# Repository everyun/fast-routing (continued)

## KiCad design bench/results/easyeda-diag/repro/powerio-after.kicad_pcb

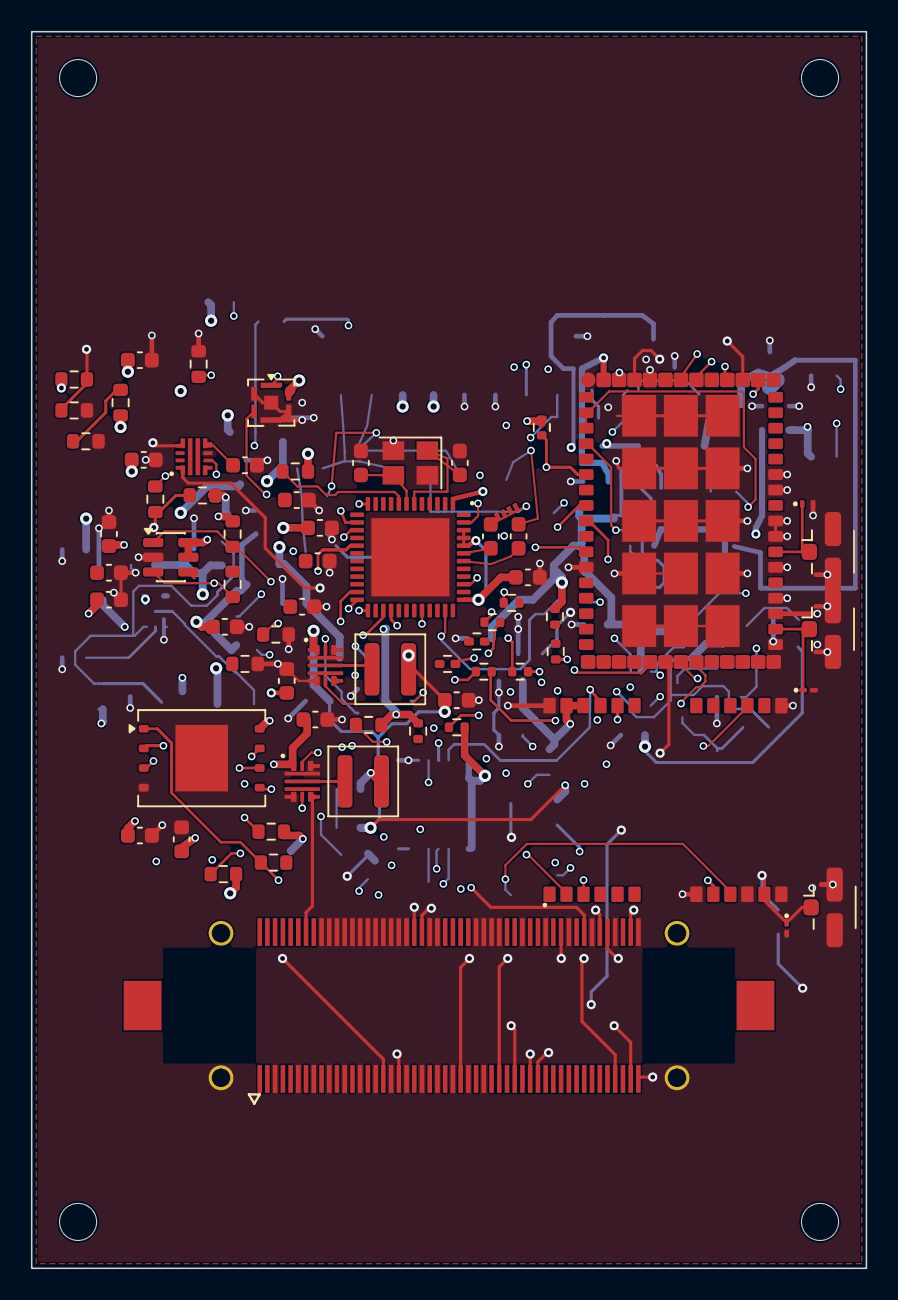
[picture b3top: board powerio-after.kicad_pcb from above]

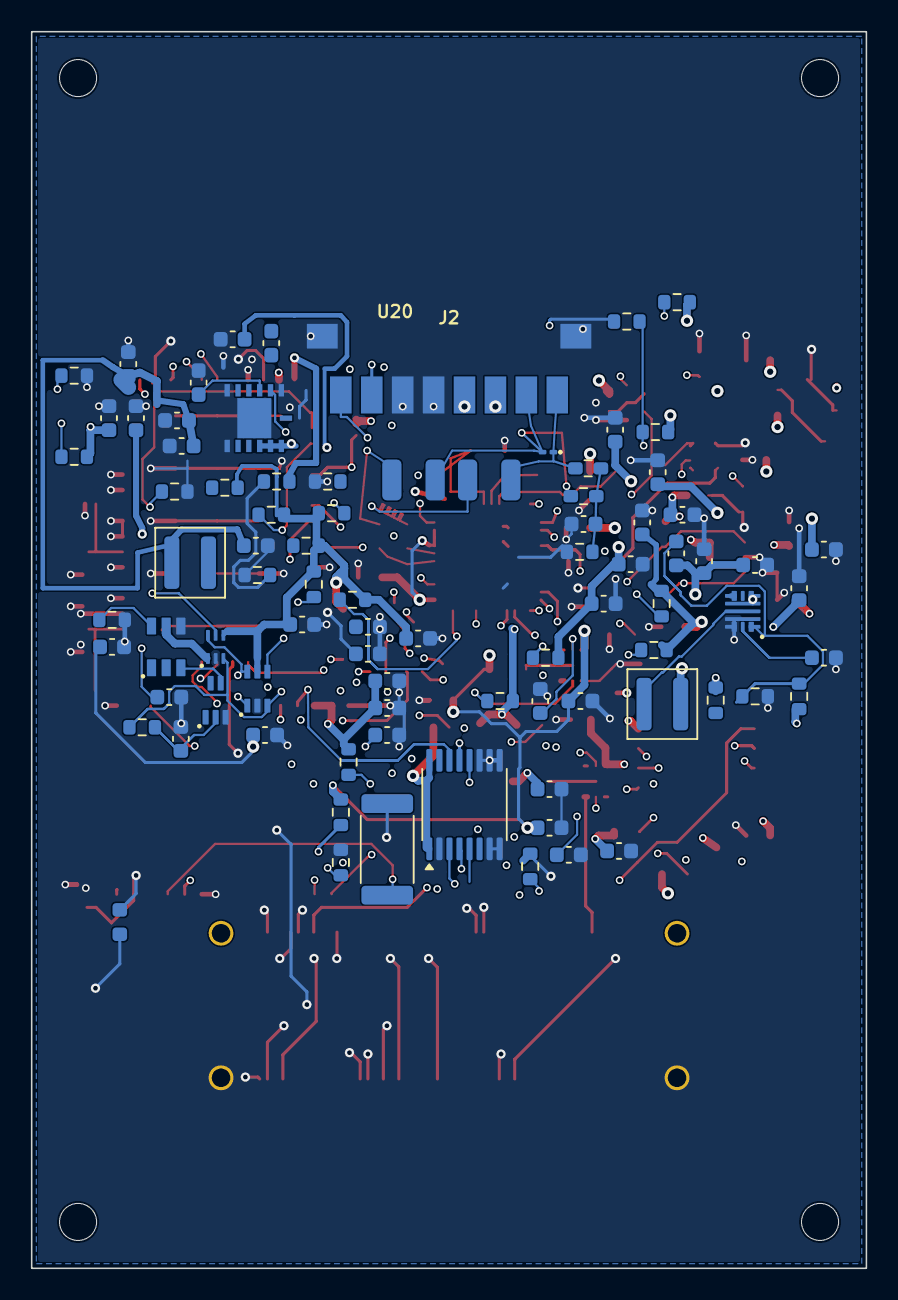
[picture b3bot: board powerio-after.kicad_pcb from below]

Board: 6 copper layers, 54.0 x 80.0 mm, 156 parts (85 on the bottom side), 117 nets.

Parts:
C101: 4.7nF; PIO_C101
C102: 22uF; PIO_C102
C103: 22uF; PIO_C103
C201: 22uF; PIO_C201
C202: 22uF; PIO_C202
C203: 22uF; PIO_C203
C204: 10uF; PIO_C204
C205: 4.7nF; PIO_C205
C301: 22uF; PIO_C301
C302: 22uF; PIO_C302
C303: 10uF; PIO_C303
C304: 4.7nF; PIO_C304
C409: 10uF; PIO_C409
C410: 100nF; PIO_C410
C411: 100nF; PIO_C411
C412: 100nF; PIO_C412
C422: 18pF; PIO_C422
C423: 18pF; PIO_C423
C430: 100nF; PIO_C430
C431: 100nF; PIO_C431
C432: 4.7nF; PIO_C432
C441: 100nF; PIO_C441
C442: 100nF; PIO_C442
C443: 100nF; PIO_C443
C444: 100nF; PIO_C444
C501: 100nF; PIO_C501
C502: 1uF; PIO_C502
C601: 10uF; PIO_C601
C602: 100nF; PIO_C602
C603: 100nF; PIO_C603
C604: 1uF; PIO_C604
C605: 1uF; PIO_C605
C606: 100nF; PIO_C606
C607: 100nF; PIO_C607
C608: 100nF; PIO_C608
C609: 4.7nF; PIO_C609
C610: 4.7nF; PIO_C610
C611: 47nF; PIO_C611
C612: 100nF; PIO_C612
C701: 1uF; PIO_C701
C702: 100nF; PIO_C702
C703: 100nF; PIO_C703
C901: 100nF; PIO_C901
C902: 4.7uF; PIO_C902
C1101: 100nF; PIO_C1101
C1102: 1nF; PIO_C1102
C1103: 4.7nF; PIO_C1103
C1301: 100nF; PIO_C1301
C1302: 100nF; PIO_C1302
C1501: 22uF; PIO_C1501
C1502: 22uF; PIO_C1502
C1503: 22uF; PIO_C1503
C1504: 10uF; PIO_C1504
C1505: 10pF; PIO_C1505
C1506: 4.7nF; PIO_C1506
C2001: 22uF; PIO_C2001
C2002: 22uF; PIO_C2002
C2003: 22uF; PIO_C2003
C2004: 100nF; PIO_C2004
C2005: 1uF; PIO_C2005
D430: PESD2ETH100-T; PIO_D430
D601: ESD; PIO_D601
D602: ESD; PIO_D602
D701: ESD; PIO_D701
J1: FX23L-100S-0.5SV-SEL; PIO_J1
J2: PIO-HYBRID-8P-RA-PIGTAIL; PIO_J2
J3: U.FL-R-SMT-1(10); PIO_J3
J4: U.FL-R-SMT-1(10); PIO_J4
J5: U.FL-R-SMT-1(10); PIO_J5
L201: 0.47uH; PIO_L201
L301: 0.47uH; PIO_L301
L430: 80uH; PIO_L430
L431: 80uH; PIO_L431
L701: 27nH; PIO_L701
L1501: 0.47uH; PIO_L1501
L2001: 4.7uH; PIO_L2001
MH1: M2_NPTH_D2.4; PIO_MH1
MH2: M2_NPTH_D2.4; PIO_MH2
MH3: M2_NPTH_D2.4; PIO_MH3
MH4: M2_NPTH_D2.4; PIO_MH4
R101: 604k; PIO_R101
R102: 100k; PIO_R102
R103: 1.27M; PIO_R103
R104: 100k; PIO_R104
R105: 1.00k; PIO_R105
R106: 10k; PIO_R106
R107: 0R; PIO_R107
R201: 10k; PIO_R201
R301: 10k; PIO_R301
R401: 1k; PIO_R401
R402: 4.7k; PIO_R402
R403: 10k; PIO_R403
R411: 33R; PIO_R411
R412: 33R; PIO_R412
R413: 33R; PIO_R413
R414: 33R; PIO_R414
R415: 33R; PIO_R415
R416: 33R; PIO_R416
R430: 12.1k; PIO_R430
R431: 10k; PIO_R431
R432: 10k; PIO_R432
R433: 10k; PIO_R433
R434: 1.00k; PIO_R434
R435: 1.00k; PIO_R435
R436: 100k; PIO_R436
R501: 4.7k; PIO_R501
R502: 4.7k; PIO_R502
R503: 4.7k; PIO_R503
R601: 100k; PIO_R601
R602: 100k; PIO_R602
R603: 100k; PIO_R603
R604: 100k; PIO_R604
R605: 100k; PIO_R605
R606: 47k; PIO_R606
R607: 47k; PIO_R607
R608: 47k; PIO_R608
R609: 47k; PIO_R609
R610: 47k; PIO_R610
R611: 10k; PIO_R611
R612: 10k; PIO_R612
R615: 100k; PIO_R615
R701: 100k; PIO_R701
R702: 10k; PIO_R702
R703: 100k; PIO_R703
R704: 22R; PIO_R704
R901: 2k; PIO_R901
R902: 2k; PIO_R902
R1101: 10k; PIO_R1101
R1102: 10k; PIO_R1102
R1501: 47.5k; PIO_R1501
R1502: 15k; PIO_R1502
R1503: 10k; PIO_R1503
R1601: 0R; PIO_R1601
R1602: 10k; PIO_R1602
R1603: 10k; PIO_R1603
R2001: 100k; PIO_R2001
R2002: 24.9k; PIO_R2002
R2003: 200k; PIO_R2003
R2004: 10k; PIO_R2004
U1: TPS259470ARPWR; PIO_U1
U2: TPS628133HQWRWYRQ1; PIO_U2
U3: TPS628112MQWRWYRQ1; PIO_U3
U4: LAN8871-V/PUAVAO; PIO_U4
U5: MX25U51245GZ4J00; PIO_U5
U6: JODY-W263-01A; PIO_U6
U7: NEO-M9L-01A-01; PIO_U7
U9: ILPS28QSWTR; PIO_U9
U11: TPS3808G18DBVR; PIO_U11
U13: SN74AXC4T774QPWRQ1; PIO_U13
U15: TPS62812QWRWYRQ1; PIO_U15
U16: TPS22995HQDDCRQ1; PIO_U16
U17: SN74LVC1G11IDCKRQ1; PIO_U17
U18: TPS389018QDSERQ1; PIO_U18
U19: SN74LVC1G17QDCKRQ1; PIO_U19
U20: LM61460AFSQRJRRQ1; PIO_U20
Y401: 25MHz CL12pF; PIO_Y401

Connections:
+1V8_AUX: C302.1, C303.1, C409.1, C410.1, C411.1, C412.1, C501.1, C502.1, C603.1, C605.1, C607.1, C608.1, C612.1, C1101.1, C1103.1, C1301.1, L301.2, R106.2, R201.2, R301.2, R401.2, R402.2, R403.2, R431.2, R433.2, R501.2, R502.2, R503.2, R602.2, R603.2, R604.2, R606.2, R607.2, R608.2, R609.2, R610.2, R612.2, R1101.2, R1102.2, R1503.2, R1602.2, R1603.2, R2004.2, U3.5, U4.13, U4.20, U4.36, U5.8, U6.3, U11.5, U11.6, U13.1, U13.16, U16.2, U17.5, U18.4, U19.5
+1V8_JODY_SW: C604.1, C610.1, U6.4, U16.5, U18.1
+2V5_PHY: C441.1, C442.1, C443.1, C444.1, C1502.1, C1503.1, C1504.1, C1505.1, L1501.2, R1501.1, U4.1, U4.5, U4.9, U4.10, U4.19, U4.29, U4.37, U4.41, U4.44, U4.45, U4.46, U4.48
+3V3_AUX: C202.1, C203.1, C204.1, C701.1, C702.1, C901.1, C902.1, C1302.1, L201.2, R701.2, R702.2, R901.2, R902.2, U2.5, U7.22, U7.23, U9.6, U13.15
+5V_PROTECTED: C103.1, C201.1, C301.1, C601.1, C602.1, C606.1, C1501.1, C2002.1, C2003.1, J1.1, J1.2, J1.3, J1.4, J1.5, J1.6, J1.7, J1.8, J1.P1, J1.P2, L2001.2, R2001.1, U2.2, U2.8, U3.2, U3.8, U6.2, U15.1, U15.2, U15.8, U16.1
+12V_PROTECTED: C2001.1, U1.6, U20.1, U20.2, U20.3
+12V_TAIL_PROTECTED: C102.1, J2.3, J2.4, R101.1, R103.1, U1.5
ACC_ON: J1.90, R1601.2, R1602.1
ACC_STATUS: J2.7, R1601.1
BT_DEV_WAKE_FROM_SOC: J1.21, U6.11
BT_HOST_WAKE_TO_SOC: J1.22, U6.12
BT_REG_ON_FROM_SOC: J1.85, U6.33
BT_RF: D602.1, J4.1, U6.24
BT_UART_CTS_N_FROM_SOC: J1.83, U6.39
BT_UART_RTS_N_TO_SOC: J1.84, U6.38
BT_UART_RX_TO_SOC: J1.82, U6.36
BT_UART_TX_FROM_SOC: J1.81, U6.37
EFUSE_DVDT: C101.1, U1.7
EFUSE_EN_UVLO: R101.2, R102.1, U1.1
EFUSE_ILM: R105.1, U1.9
EFUSE_OVLO: R103.2, R104.1, U1.2
EPHY0_RSTN: J1.54, R403.1, U4.39
FB_2V5_PHY: C1505.2, R1501.2, R1502.1, U15.5
GND: C101.2, C102.2, C103.2, C201.2, C202.2, C203.2, C204.2, C205.2, C301.2, C302.2, C303.2, C304.2, C409.2, C410.2, C411.2, C412.2, C422.2, C423.2, C432.2, C441.2, C442.2, C443.2, C444.2, C501.2, C502.2, C601.2, C602.2, C603.2, C604.2, C605.2, C606.2, C607.2, C608.2, C609.2, C610.2, C611.2, C612.2, C701.2, C702.2, C703.2, C901.2, C902.2, C1101.2, C1102.2, C1103.2, C1301.2, C1302.2, C1501.2, C1502.2, C1503.2, C1504.2, C1506.2, C2001.2, C2002.2, C2003.2, C2005.2, D601.2, D602.2, D701.2, J1.9, J1.10, J1.11, J1.12, J1.13, J1.14, J1.15, J1.16, J1.17, J1.18, J1.19, J1.20, J1.23, J1.24, J1.29, J1.30, J1.31, J1.32, J1.35, J1.38, J1.41, J1.44, J1.47, J1.50, J1.53, J1.56, J1.58, J1.60, J1.62, J1.64, J1.66, J1.68, J1.70, J1.72, J1.74, J1.76, J1.78, J1.80, J1.P3, J1.P4, J2.5, J2.6, J2.SH1, J2.SH2, J3.2, J4.2, J5.2, R102.2, R104.2, R105.2, R430.2, R432.2, R436.2, R601.2, R605.2, R611.2, R703.2, R1502.2, R2002.2, R2003.2, U1.8, U2.1, U2.4, U2.7, U3.1, U3.4, U3.7, U4.49, U5.4, U5.9, U6.1, U6.5, U6.19, U6.20, U6.22, U6.23, U6.25, U6.27, U6.28, U6.30, U6.31, U6.49, U6.61, U6.62, U6.63, U6.64, U6.65, U6.66, U6.67, U6.68, U6.69, U6.70, U6.71, U6.72, U6.73, U6.74, U6.75, U7.7, U7.10, U7.12, U7.13, U7.24, U9.2, U9.4, U9.5, U9.7, U11.2, U13.2, U13.7, U13.8, U13.9, U13.10, U13.11, U15.4, U15.7, U16.4, U17.2, U18.2, U19.3, U20.6, U20.7, U20.12, U20.14, Y401.2, Y401.4
GNSS_1PPS_TO_SOC: J1.97, U13.5
GNSS_BIAS_LIMITED: L701.1, R704.2
GNSS_DIR: R703.1, U7.15
GNSS_DSEL_HI: R701.1, U7.2
GNSS_RESET_N: R702.1, U7.8
GNSS_RF: D701.1, J5.1, L701.2, U7.11
GNSS_RX_3V3: U7.21, U13.14
GNSS_TIMEPULSE_3V3: U7.3, U13.12
GNSS_TX_3V3: U7.20, U13.13
GNSS_TX_TO_SOC_UART2_RX: J1.95, U13.4
GNSS_VCC_RF: C703.1, R704.1, U7.9
I2C11_SCL_3V3_OD: J1.93, R902.1, U9.3
I2C11_SDA_3V3_OD: J1.94, R901.1, U9.1
JODY_1V8_CT: C609.1, U18.5
JODY_1V8_GOOD: R612.1, U17.6, U18.6
JODY_1V8_RT: R611.1, U16.6
JODY_CONFIG0_PD: R601.1, U6.7
JODY_CONFIG1_HI: R602.1, U6.8
JODY_CONFIG2_DNI: R603.1, U6.6
JODY_PDN_GATED: R605.1, U6.58, U6.59, U17.4
JODY_PG_DELAYED: U16.3, U19.4
JODY_PG_DELAY_RC: C611.1, R615.2, U19.2
JODY_PG_N: R604.1, R615.1, U6.57, U17.3, U18.3
MDCK: J1.52, U4.34
MDIO: J1.51, R401.1, U4.33
PG_1V8_N: R301.1, U3.9
PG_2V5_PHY_N: R1503.1, U15.9
PG_3V3_N: R201.1, U2.9
PG_5V0_N: R2004.1, U20.11
PHY_EXTRES: R430.1, U4.47
PHY_INT_N: R402.1, U4.35
PHY_MODE_STRP: R432.1, U4.18
PHY_REG_EN: R431.1, U4.8
PHY_RXCK: R416.1, U4.16
PHY_RXD0: R411.1, U4.11
PHY_RXD1: R412.1, U4.12
PHY_RXD2: R413.1, U4.14
PHY_RXD3: R414.1, U4.15
PHY_RXDV: R415.1, U4.17
PHY_SPEED_SEL: R433.1, U4.32
PHY_XI: C422.1, U4.6, Y401.1
PHY_XO: C423.1, U4.7, Y401.3
POR_CT: C1102.1, U11.4
PWR_FAIL: J1.91, J2.8, R107.2, R1603.1
PWR_FAIL_EFUSE_N: R106.1, R107.1, U1.4
RGMII0_RXCK: J1.42, R416.2
RGMII0_RXD0: J1.43, R411.2
RGMII0_RXD1: J1.45, R412.2
RGMII0_RXD2: J1.46, R413.2
RGMII0_RXD3: J1.48, R414.2
RGMII0_RXDV: J1.49, R415.2
RGMII0_TXCKOUT: J1.33, U4.23
RGMII0_TXD0: J1.34, U4.25
RGMII0_TXD1: J1.36, U4.26
RGMII0_TXD2: J1.37, U4.27
RGMII0_TXD3: J1.39, U4.28
RGMII0_TXEN: J1.40, U4.24
SFC_CLK: J1.59, U5.6
SFC_CS0N: J1.57, R501.1, U5.1
SFC_HOLD_IO3: J1.67, R503.1, U5.7
SFC_MISO_IO1: J1.63, U5.2
SFC_MOSI_IO0: J1.61, U5.5
SFC_WP_IO2: J1.65, R502.1, U5.3
SOC_UART2_TX_TO_GNSS_RX: J1.96, U13.3
SS_1V8: C304.1, U3.6
SS_2V5_PHY: C1506.1, U15.6
SS_3V3: C205.1, U2.6
SW_1V8: L301.1, U3.3
SW_2V5_PHY: L1501.1, U15.3
SW_3V3: L201.1, U2.3
SW_5V0: C2004.2, L2001.1, U20.8
SYS_RSTN: J1.86, R1101.1, U11.1
SYS_RSTN_OUT_WDG_RSTN: J1.87, R1102.1, U11.3
T1_CM_MID: C432.1, R434.2, R435.2, R436.1
T1_CON_N: D430.2, J2.2, L431.2, R435.1
T1_CON_P: D430.1, J2.1, L430.2, R434.1
T1_N: C431.1, U4.42
T1_P: C430.1, U4.43
T1_TERM_N: C431.2, L431.1
T1_TERM_P: C430.2, L430.1
U20_BOOT: C2004.1, U20.9
U20_FB: R2001.2, R2002.1, U20.5
U20_RT: R2003.1, U20.4
U20_VCC: C2005.1, U20.10
WIFI_HOST_WAKE_TO_SOC: J1.100, U6.10
WIFI_PDN_FROM_SOC: J1.99, U17.1
WIFI_RF: D601.1, J3.1, U6.29
WIFI_SDIO_CLK: J1.69, U6.53
WIFI_SDIO_CMD: J1.71, R606.1, U6.52
WIFI_SDIO_D0: J1.73, R607.1, U6.54
WIFI_SDIO_D1: J1.75, R608.1, U6.55
WIFI_SDIO_D2: J1.77, R609.1, U6.50
WIFI_SDIO_D3: J1.79, R610.1, U6.51

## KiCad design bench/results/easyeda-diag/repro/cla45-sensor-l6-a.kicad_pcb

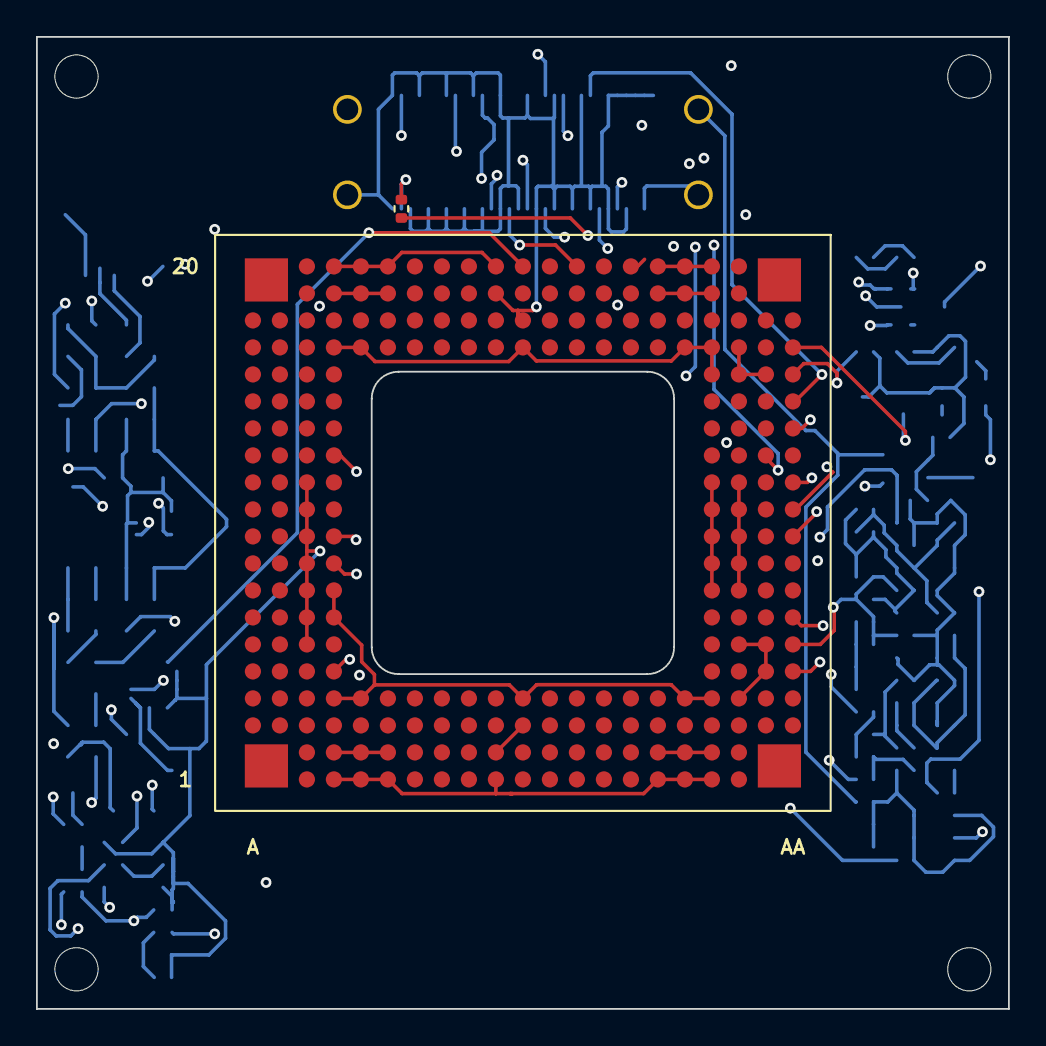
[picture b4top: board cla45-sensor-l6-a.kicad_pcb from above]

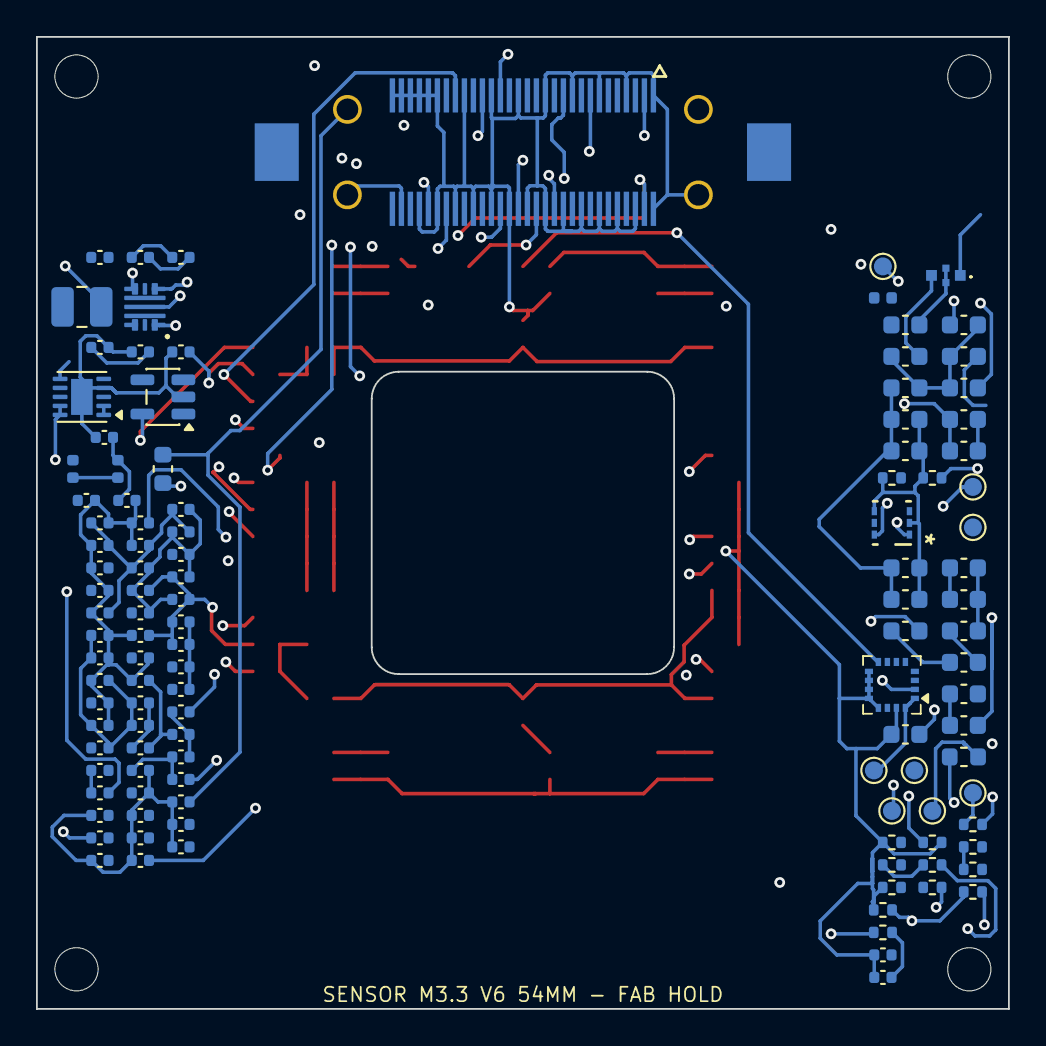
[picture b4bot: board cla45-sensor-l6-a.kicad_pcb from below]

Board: 6 copper layers, 54.0 x 54.0 mm, 120 parts (118 on the bottom side), 63 nets.

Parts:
C1, C3, C4, C6, C8, C17, C18, C24, C27, C28, C29, C34, C36, C38, C43, C47, C50, C52, C53, C58, C61, C62, C67: 1uF; C_0402_1005Metric
C2, C9, C16, C22, C23, C31, C33, C41, C45, C46, C49, C54, C55, C56, C57, C59, C63, C64, C65, C66, C70, C72: 100nF; C_0402_1005Metric
C5, C7: 2.2uF; C_0603_1608Metric
C10, C13, C19, C21, C25, C26, C32, C35, C37, C39, C44, C48: 4.7uF; C_0603_1608Metric
C11: NFM18CC101R1C3D
C12: 22uF; C_0603_1608Metric
C14, C69: 10uF; C_0603_1608Metric
C15, C79: 22uF 10V X5R; C_0603_1608Metric
C20, C30, C40, C42, C51, C60: 1000pF; C_0402_1005Metric
C68: 10nF; C_0402_1005Metric
C71: 100nF IAM VDDIO; C_0402_1005Metric
C73: 2.2uF IAM VDD; C_0402_1005Metric
C74: 100nF IAM REGOUT; C_0402_1005Metric
C75: 470nF IAM bulk; C_0402_1005Metric
C76: 4.7nF C0G; C_0402_1005Metric
C77: 10pF C0G; C_0402_1005Metric
C78: 10uF 6.3V X7T; C_0603_1608Metric
C80: 100nF X7R; C_0402_1005Metric
FB1, FB3: BLM18KG102SN1D; L_0603_1608Metric
FB2: BLM15AX300SN1D; L_0402_1005Metric
FB4, FB5: 0R EVT; L_0402_1005Metric
J_CAM: FX23L-60P-0.5SV8-SEL
L1: DFE252012PD-R47M=P2; L_1008_2520Metric
MH1, MH2, MH3, MH4: M2 NPTH Ø2.4 / ALL-CU KEEPOUT Ø6.0; M2_NPTH_D2.4
R1, R2: 47K; R_0402_1005Metric
R3, R4: 68k 0.1%; R_0402_1005Metric
R5: 22R INCK source isolation (SI tune); R_0402_1005Metric
R8, R10: 10K; R_0402_1005Metric
R11: 3.01K; R_0402_1005Metric
R12: 1.15K; R_0402_1005Metric
R13: 8.06k 1%; R_0402_1005Metric
R14: 10k 1%; R_0402_1005Metric
R15, R16, R17: 5.1k 1%; R_0402_1005Metric
R18: 10k CAM_PRESENT strap; R_0402_1005Metric
TP1, TP2, TP3, TP4, TP9, TP10: TestPoint; TestPoint_Pad_D1.0mm
TP11: RSVD_CTRL0 DNP TEST; TestPoint_Pad_D1.0mm
TP12: RSVD_CTRL1 DNP TEST; TestPoint_Pad_D1.0mm
U1: TPS62812QWRWYRQ1; TPS62812_RWY0009A
U2: IMX294
U3: LP5907MFX-1.8; SOT-23-5
U4: TPS7A90; Texas_S-PDSO-N10_EP1.2x2mm
U6: TMP117AIDRVR
U8: IAM-20680HP; IAM-20680HP_LGA16

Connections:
+1V2_RAW: C77.1, C78.1, FB4.1, FB5.1, L1.2, R3.1
+3V3_1V2_BUCK_IN: C15.1, FB3.1, U1.1, U1.2
+3V3_2V9_LDO_IN: C11.3, C14.1, U4.6, U4.9, U4.10
+3V3_SENSOR: C11.1, C72.1, FB1.1, FB3.2, J_CAM.P1, J_CAM.P2, TP4.1
AUX_I2C_SCL: J_CAM.46, R15.1, U6.1 (SCL), U8.2
AUX_I2C_SDA: J_CAM.48, R16.1, U6.6 (SDA), U8.3
CAM_PRESENT: J_CAM.56, R18.1
CAM_PWR_EN: J_CAM.54, R10.1, TP9.1, U1.8, U3.3, U4.7
COMP_1V2: R13.1, U1.7
FB_1V2: C77.2, R3.2, R4.1, U1.5
GND: C1.2, C2.2, C3.2, C4.2, C5.2, C6.2, C7.2, C8.2, C9.2, C10.1, C11.2, C12.1, C13.2, C14.2, C15.2, C16.2, C17.1, C18.1, C19.1, C20.1, C21.1, C22.2, C23.2, C24.2, C25.1, C26.1, C27.1, C28.1, C29.1, C30.1, C31.2, C32.1, C33.2, C34.2, C35.1, C36.1, C37.1, C38.1, C39.1, C40.1, C41.2, C42.1, C43.2, C44.1, C45.1, C46.2, C47.1, C48.1, C49.2, C50.1, C51.1, C52.1, C53.1, C54.1, C55.2, C56.2, C57.1, C58.1, C59.1, C60.1, C61.1, C62.1, C63.2, C64.2, C65.1, C66.1, C67.2, C69.2, C70.1, C71.2, C72.2, C73.2, C74.2, C75.2, C76.2, C78.2, C79.2, C80.2, J_CAM.1, J_CAM.4, J_CAM.7, J_CAM.10, J_CAM.13, J_CAM.16, J_CAM.19, J_CAM.22, J_CAM.25, J_CAM.26, J_CAM.27, J_CAM.28, J_CAM.29, J_CAM.30, J_CAM.31, J_CAM.33, J_CAM.35, J_CAM.37, J_CAM.39, J_CAM.41, J_CAM.43, J_CAM.45, J_CAM.47, J_CAM.49, J_CAM.51, J_CAM.53, J_CAM.55, J_CAM.57, J_CAM.59, J_CAM.P3, J_CAM.P4, R1.2, R2.2, R4.2, R10.2, R12.1, R13.2, R18.2, U1.4, U2.C4, U2.C6, U2.C7, U2.C8, U2.C9, U2.C10, U2.C11, U2.C12, U2.C15, U2.C17, U2.D2, U2.D19, U2.E2, U2.E19, U2.F2, U2.F19, U2.K2, U2.K19, U2.L3, U2.L18, U2.T2, U2.T19, U2.U2, U2.U19, U2.V2, U2.V19, U2.W4, U2.W6, U2.W8, U2.W9, U2.W10, U2.W11, U2.W12, U2.W16, U2.W17, U2.Y5, U2.Y6, U2.Y16, U3.2, U4.4, U4.11, U6.2 (GND), U6.4 (ADD0), U8.4, U8.9, U8.10, U8.11, U8.12, U8.13, U8.15
IMU_INT1: J_CAM.50, U8.6
IMU_REGOUT: C74.1, U8.14
INCK_72MHZ: J_CAM.32, R5.1
INCK_SENSOR: R5.2, U2.AA5
NR_SS_2V9: C67.1, U4.8
unnamed: C1.1, U2.C16
unnamed: C3.1, U2.D5
unnamed: C4.1, U2.D16
unnamed: C8.1, U2.C5
unnamed: C2.1, U2.V15
unnamed: C9.1, U2.C14
unnamed: R2.1, U2.V14
unnamed: R1.1, U2.D13
unnamed: C6.1, U2.D10
unnamed: C7.1, U2.D11
unnamed: C5.1, U2.D9
unnamed: C10.2, FB1.2, U3.1
unnamed: C68.1, R11.1, R12.2, U4.3
PG_1V2_N: R14.1, U1.9
RST_1V8: R8.2, TP10.1
RSVD_CTRL0: J_CAM.58, TP11.1
RSVD_CTRL1: J_CAM.60, TP12.1
SCK: J_CAM.34, U2.P20
SDI: J_CAM.36, U2.R20
SLVS_D0_N: J_CAM.3, U2.Y7
SLVS_D0_P: J_CAM.2, U2.AA7
SLVS_D1_N: J_CAM.6, U2.Y8
SLVS_D1_P: J_CAM.5, U2.AA8
SLVS_D2_N: J_CAM.9, U2.Y10
SLVS_D2_P: J_CAM.8, U2.AA10
SLVS_D3_N: J_CAM.12, U2.Y11
SLVS_D3_P: J_CAM.11, U2.AA11
SLVS_D4_N: J_CAM.15, U2.Y12
SLVS_D4_P: J_CAM.14, U2.AA12
SLVS_D5_N: J_CAM.18, U2.Y13
SLVS_D5_P: J_CAM.17, U2.AA13
SLVS_D6_N: J_CAM.21, U2.Y14
SLVS_D6_P: J_CAM.20, U2.AA14
SLVS_D7_N: J_CAM.24, U2.Y15
SLVS_D7_P: J_CAM.23, U2.AA15
SS_1V2: C76.1, U1.6
SW_1V2: L1.1, U1.3
TEMP_1V8: C70.2, FB2.2, U6.5 (V+)
TEMP_ALERT: J_CAM.52, R17.1, U6.3 (ALERT)
VADD_2V9: C19.2, C25.2, C28.2, C32.2, C36.2, C37.2, C44.2, C45.2, C48.2, C57.2, C59.2, C65.2, C66.2, C68.2, C69.1, R11.2, TP3.1, U2.D4, U2.D7, U2.D8, U2.D17, U2.E4, U2.E17, U2.L4, U2.L17, U2.U4, U2.U17, U2.V4, U2.V16, U2.V17, U4.1, U4.2
VDDD1_1V2: C12.2, C17.2, C18.2, C20.2, C21.2, C22.1, C23.1, C24.1, C26.2, C27.2, C29.2, C30.2, C31.1, C33.1, C34.1, C35.2, C38.2, C39.2, C40.2, C41.1, C42.2, C43.1, C46.1, C47.2, C49.1, C50.2, C51.2, C52.2, C53.2, C55.1, C56.1, C58.2, C60.2, C61.2, C62.2, C63.1, C64.1, FB4.2, TP1.1, U2.AA6, U2.AA16, U2.D1, U2.D20, U2.E1, U2.E20, U2.F1, U2.F20, U2.K1, U2.K20, U2.T1, U2.T20, U2.U1, U2.U20, U2.V1, U2.V6, U2.V20
VDDD2_1V8: C13.1, C16.1, C54.2, C71.1, C73.1, C75.1, FB2.1, R8.1, R14.2, R15.2, R16.2, R17.2, TP2.1, U2.AA17, U3.5, U8.1, U8.5, U8.16
VDDD3_1V2: C79.1, C80.1, FB5.2, U2.V8, U2.V9, U2.V10, U2.V11, U2.V12
XCE: J_CAM.38, U2.L19
XCLR: J_CAM.40, U2.P19
XHS: J_CAM.44, U2.N20
XVS: J_CAM.42, U2.L20, U8.8
